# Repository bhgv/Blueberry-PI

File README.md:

to use with spi-nand flash build & flash this Linux tree:

* OpenWRT: https://github.com/bhgv/openwrt

***

main build board now is `Blueberry Pi 7.1.2.esp32.no-lan.gsm-a9g`. because `a9g` gsm module is much better then `sim800c`. because of open source SDK and support of GPS.

but still work-in-progress. not finished.

sources of Linux kernel (4.10.15) for this board(s). preconfigured:
https://github.com/bhgv/linux

precompiled Linux-4.10.15 SD-image with support of fb-graphics an resistive touch:
https://github.com/bhgv/linux/releases/tag/1.0a

exp2_Blueberry Pi 7.1.2.licheepi-zero.esp32.no-lan.gsm-a9g.no-50p
=================================================================
most simplest to assembly choise
* cheap Lichee Pi zero module as CPU and CPU-power module. also used its TFT connector
* ESP32-WROOM as wifi/bluetooth module
* A9/A9G as GSM/GPS module
* connector for cheap popular gt911 capacitive touchscreens (workable driver for gt911 is included to [this Linux](https://github.com/bhgv/linux))
* includes Li-Ion/polimer battery charging/powering circuits

Blueberry Pi 7.1.2.esp32.no-lan
===============================
(not finished yet)
* removed lan port,
* added 50pins fpc RGB connector for popular 7" tfts (AT070TN[90, 91, 92, 93, 94]) in parallel to 40pins one,
* connector for capacitive touchscreens (i2c1),
* power converters for 50pins socket,
* 25% smaller board.
* esp32 now wired as wifi/bluetooth and as io expander-coprocessor.

Blueberry Pi 7.1.1+ESP32-S
==========================
(not finised yet)
* other power controller(s). 3 cheap and easy to solder chips in sot23-6,
* a try to use ESP32-S module as a WiFi/Bluetooth co-processor.

List of compatible (and cheap) LCDs (with touchscreens)
=======================================================
* ? 7" -- MDT7000
* 7" -- TKR7040B
* 7" -- GL070009T0-40

* 6" -- KD060G1-40nc-a5
* 6" -- TM060RDH02

* 5" -- HSD050IDW1-A20
* 5" -- MH0506D
* 5" -- KD50G21-40NT-A1
* 5" -- A26TF9C032169 * A0 -A20
* 5" -- H-H050L-12M
* 5" -- GL050001C0-40
* 5" -- ft050s800480005n-v01
* 5" -- HW800480F-0F-0L-20
* 5" -- hw800480f-0f-0l-10
* 5" -- T050SWV012T
* 5" -- T050SWV015T
* 5" -- FC050S151-01
* 5" -- KD50G23-40NB-A1
* 5" -- HLY050ML115-12A

(
* 6" -- texet tn-811bt

* 5" --
- Window N5 TOP Tablet PC/ N5PRO/ Onda 580
- TeXet T-939HD
- TeXet T-930HD
- TeXet TN-550A
- TeXet TN-511HD
- TeXet TN-521HD
- TeXet TN-610HD
- TeXet TN-611HD
- TeXet TM-650 (100%)
- Explay PN-955
- Explay PN-960
- SHTURMANN Play 500
- IQU Smile
- Lexand Si-515 Pro HD
- Lexand SG-615 PRO HD
- Ritmix
- EasyGo 500Bi (100%)
- lexand str-5350 hd (100%)
- Prestigio Geovision 5500BTFMHD (100%)
- Prestigio GeoVision 5600GPRSHD
- Explay SLK5
- JXD S5300
- TurboGames New
- EXEQ SET
)

Blueberry Pi 7.1+axp203
=======================
is the Blueberry Pi 7.1 board but with AXP203 power controller, not EA3036. and has DC-DC step down (5-12v) on power input.

Blueberry PI 7.1
================

Added:
------
* LVDS interface with cheap SN65LVDS84 serialiser,
* resistive touchscreen controller TSC2003 + pinheader for resistive touch,
* flash w25q128,
* more popular MicroSD card slot,
* datasheets for them

Removed:
--------
* pinheader for OV7670

Blueberry PI
============
Another fruit single board computer (SBC), based on the Allwinner V3s system on a chip (SOC).
The Allwinner V3s comes in an easy to solder 128pin TQFP package.

The Blueberry PI features:

- 100 mbps Ethernet
- 1 USB Host Port / 1 mini USB port
- MIPI CSI interface (unfortunately no support in the linux kernel yet)
- Pinheader for an OV2640 and an OV7670
- Wifi and bluetooth
- RGB interface for connecting displays
- Audio jack
- an onboard microphone
- four buttons for play, pause, next and previous
- a Raspberry PI compatible header
- SPI Flash
- SD card slot

The Blueberry PI can boot from an SD card or SPI Flash.
Since the V3s doesn't have a standard video output, I'm planning on creating a video addon board which provides VGA or HDMI. In combination with the ADV7611 it is possible to capture HDMI.

If you have any questions email me at marcel[dot]thuermer(at)smail[dot]emt[dot]h[minus]brs[dot]de

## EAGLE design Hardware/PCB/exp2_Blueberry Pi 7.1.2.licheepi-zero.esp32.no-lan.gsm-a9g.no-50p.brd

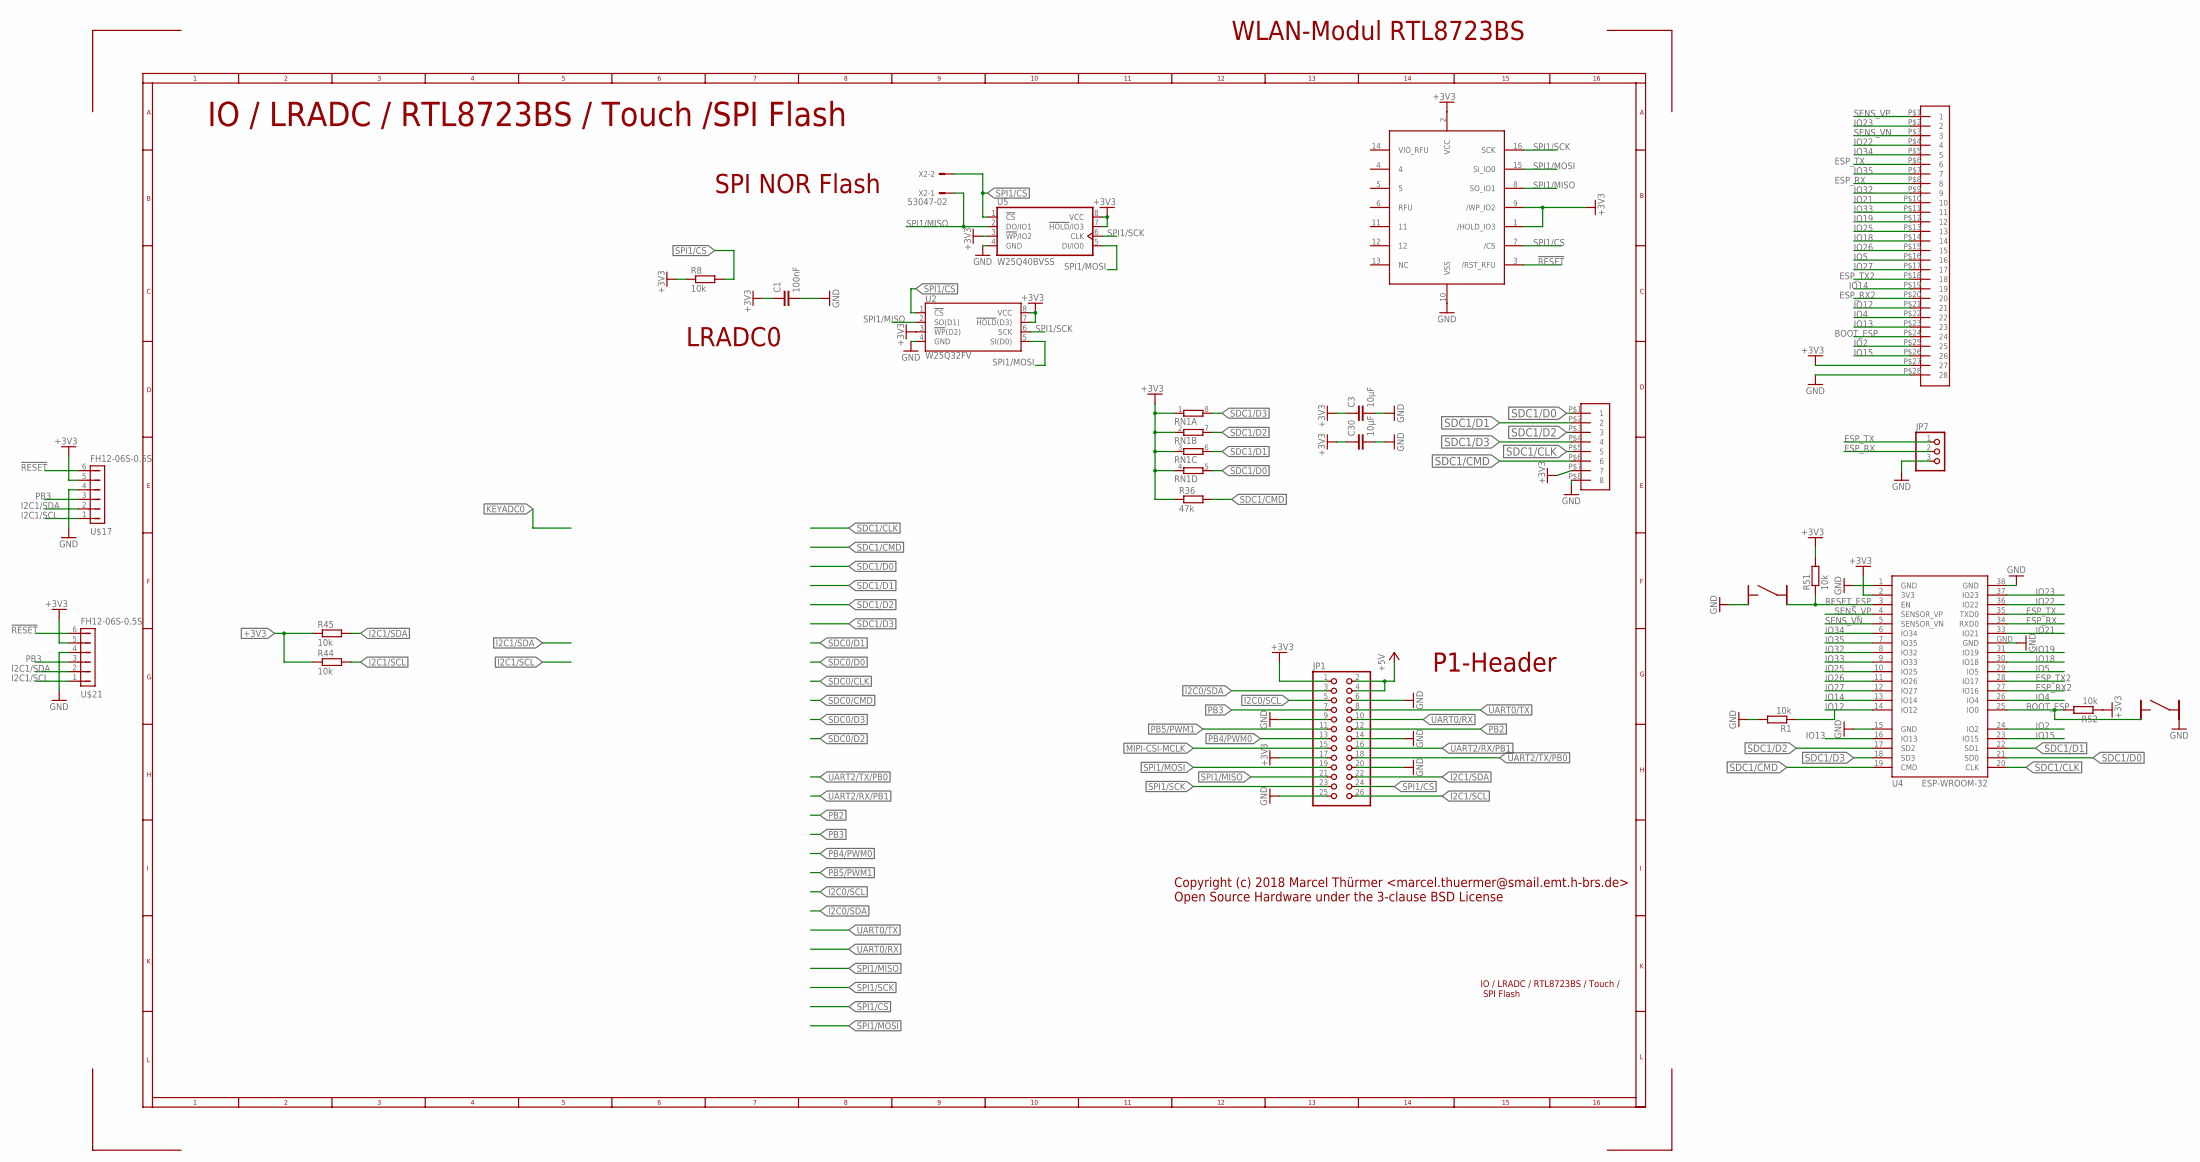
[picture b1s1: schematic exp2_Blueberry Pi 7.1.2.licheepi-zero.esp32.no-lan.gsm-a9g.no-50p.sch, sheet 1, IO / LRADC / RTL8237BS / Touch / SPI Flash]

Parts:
C1: 100nF; C0603
C3, C30: 10µF; C0805
JP1: PINHD-2X13; 2X13
JP7: PINHD-1X3M; 1X03M
R1, R8, R44, R45, R51, R52: 10k; R0603
R36: 47k; R0603
RN1: 4R-NEXB38V; EXB38V
S-BOOT-ESP: BUTTON_3X3MM_4PINS; BUT_3X3_4PINS
S-RST-ESP: BUTTON_3X3MM_4PINS; BUT_3X3_4PINS
U2: W25Q32FV; WSON8-6X5MM
U4: ESP-WROOM-32
U5: W25Q40BVSS; SO08-SS
U$3: HDR-1.27MM-142; HDR-1.27MM-19*2
U$4: HDR-1.27MM-42; HDR-1.27MM-4*2
U$16: S25FL256S; WSOIC-16
U$17, U$21: FH12-06S-0.5S; FH12-6S-0.5SH
X2: 53047-02

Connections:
!RESET: U$16.3 (/RST_RFU), U$17.6, U$21.6; also elsewhere on the board
+3V3: C1.1, C3.1, C30.1, JP1.1, JP1.17, R8.1, R36.1, R44.1, R45.1, R51.2, R52.1, RN1.1, RN1.2 (1), RN1.3 (1), RN1.4 (1), U2.3 (!WP!(D2)), U2.7 (!HOLD!(D3)), U2.8 (VCC), U4.2 (3V3), U5.3 (!WP!/IO2), U5.7 (!HOLD!/IO3), U5.8 (VCC), U$3.P$27 (27), U$4.P$7 (7), U$16.1 (/HOLD_IO3), U$16.2 (VCC), U$16.9 (/WP_IO2), U$17.5, U$21.5; also elsewhere on the board
+5V: JP1.2, JP1.4; also elsewhere on the board
BOOT_ESP: R52.2, S-BOOT-ESP.P$1, U4.25 (IO0), U$3.P$24 (24)
ESP_RX: JP7.2, U4.34 (RXD0), U$3.P$8 (8)
ESP_RX2: U4.27 (IO16), U$3.P$20 (20); also elsewhere on the board
ESP_TX: JP7.1, U4.35 (TXD0), U$3.P$6 (6)
ESP_TX2: U4.28 (IO17), U$3.P$18 (18); also elsewhere on the board
GND: C1.2, C3.2, C30.2, JP1.6, JP1.9, JP1.14, JP1.20, JP1.25, JP7.3, R1.2, S-BOOT-ESP.P$2, S-RST-ESP.P$1, U2.4 (GND), U4.1 (GND), U4.15 (GND), U4.38 (GND), U4.GND, U5.4 (GND), U$3.P$28 (28), U$4.P$8 (8), U$16.10 (VSS), U$17.4, U$21.4; also elsewhere on the board
I2C0/SCL: JP1.5; also elsewhere on the board
I2C0/SDA: JP1.3; also elsewhere on the board
I2C1/SCL: JP1.26, R44.2, U$17.1, U$21.1; also elsewhere on the board
I2C1/SDA: JP1.22, R45.2, U$17.2, U$21.2; also elsewhere on the board
IO2: U4.24 (IO2), U$3.P$25 (25)
IO4: U4.26 (IO4), U$3.P$22 (22)
IO5: U4.29 (IO5), U$3.P$16 (16)
IO12: R1.1, U4.14 (IO12), U$3.P$21 (21)
IO13: U4.16 (IO13), U$3.P$23 (23)
IO14: U4.13 (IO14), U$3.P$19 (19); also elsewhere on the board
IO15: U4.23 (IO15), U$3.P$26 (26)
IO18: U4.30 (IO18), U$3.P$14 (14)
IO19: U4.31 (IO19), U$3.P$12 (12)
IO21: U4.33 (IO21), U$3.P$10 (10)
IO22: U4.36 (IO22), U$3.P$4 (4)
IO23: U4.37 (IO23), U$3.P$2 (2)
IO25: U4.10 (IO25), U$3.P$13 (13)
IO26: U4.11 (IO26), U$3.P$15 (15)
IO27: U4.12 (IO27), U$3.P$17 (17); also elsewhere on the board
IO32: U4.8 (IO32), U$3.P$9 (9)
IO33: U4.9 (IO33), U$3.P$11 (11)
IO34: U4.6 (IO34), U$3.P$5 (5)
IO35: U4.7 (IO35), U$3.P$7 (7)
MIPI-CSI-MCLK: JP1.15
PB2: JP1.12; also elsewhere on the board
PB3: JP1.7, U$17.3, U$21.3; also elsewhere on the board
PB4/PWM0: JP1.13; also elsewhere on the board
PB5/PWM1: JP1.11; also elsewhere on the board
RESET_ESP: R51.1, S-RST-ESP.P$2, U4.3 (EN)
SDC1/CLK: U4.20 (CLK), U$4.P$5 (5); also elsewhere on the board
SDC1/CMD: R36.2, U4.19 (CMD), U$4.P$6 (6); also elsewhere on the board
SDC1/D0: RN1.5 (2), U4.21 (SD0), U$4.P$1 (1); also elsewhere on the board
SDC1/D1: RN1.6 (2), U4.22 (SD1), U$4.P$2 (2); also elsewhere on the board
SDC1/D2: RN1.7 (2), U4.17 (SD2), U$4.P$3 (3); also elsewhere on the board
SDC1/D3: RN1.8 (2), U4.18 (SD3), U$4.P$4 (4); also elsewhere on the board
SENS_VN: U4.5 (SENSOR_VN), U$3.P$3 (3)
SENS_VP: U4.4 (SENSOR_VP), U$3.P$1 (1)
SPI1/CS: JP1.24, R8.2, U2.1 (!CS!), U5.1 (!CS!), U$16.7 (/CS), X2.2; also elsewhere on the board
SPI1/MISO: JP1.21, U2.2 (SO(D1)), U5.2 (DO/IO1), U$16.8 (SO_IO1), X2.1; also elsewhere on the board
SPI1/MOSI: JP1.19, U2.5 (SI(D0)), U5.5 (DI/IO0), U$16.15 (SI_IO0); also elsewhere on the board
SPI1/SCK: JP1.23, U2.6 (SCK), U5.6 (CLK), U$16.16 (SCK); also elsewhere on the board
UART0/RX: JP1.10; also elsewhere on the board
UART0/TX: JP1.8; also elsewhere on the board
UART2/RX/PB1: JP1.16; also elsewhere on the board
UART2/TX/PB0: JP1.18; also elsewhere on the board

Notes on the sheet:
IO / LRADC / RTL8723BS / Touch / SPI Flash
Copyright (c) 2018 Marcel Thürmer <marcel.thuermer@smail.emt.h-brs.de> Open Source Hardware under the 3-clause BSD License
SPI NOR Flash
WLAN-Modul RTL8723BS
P1-Header
LRADC0
IO / LRADC / RTL8723BS / Touch /SPI Flash

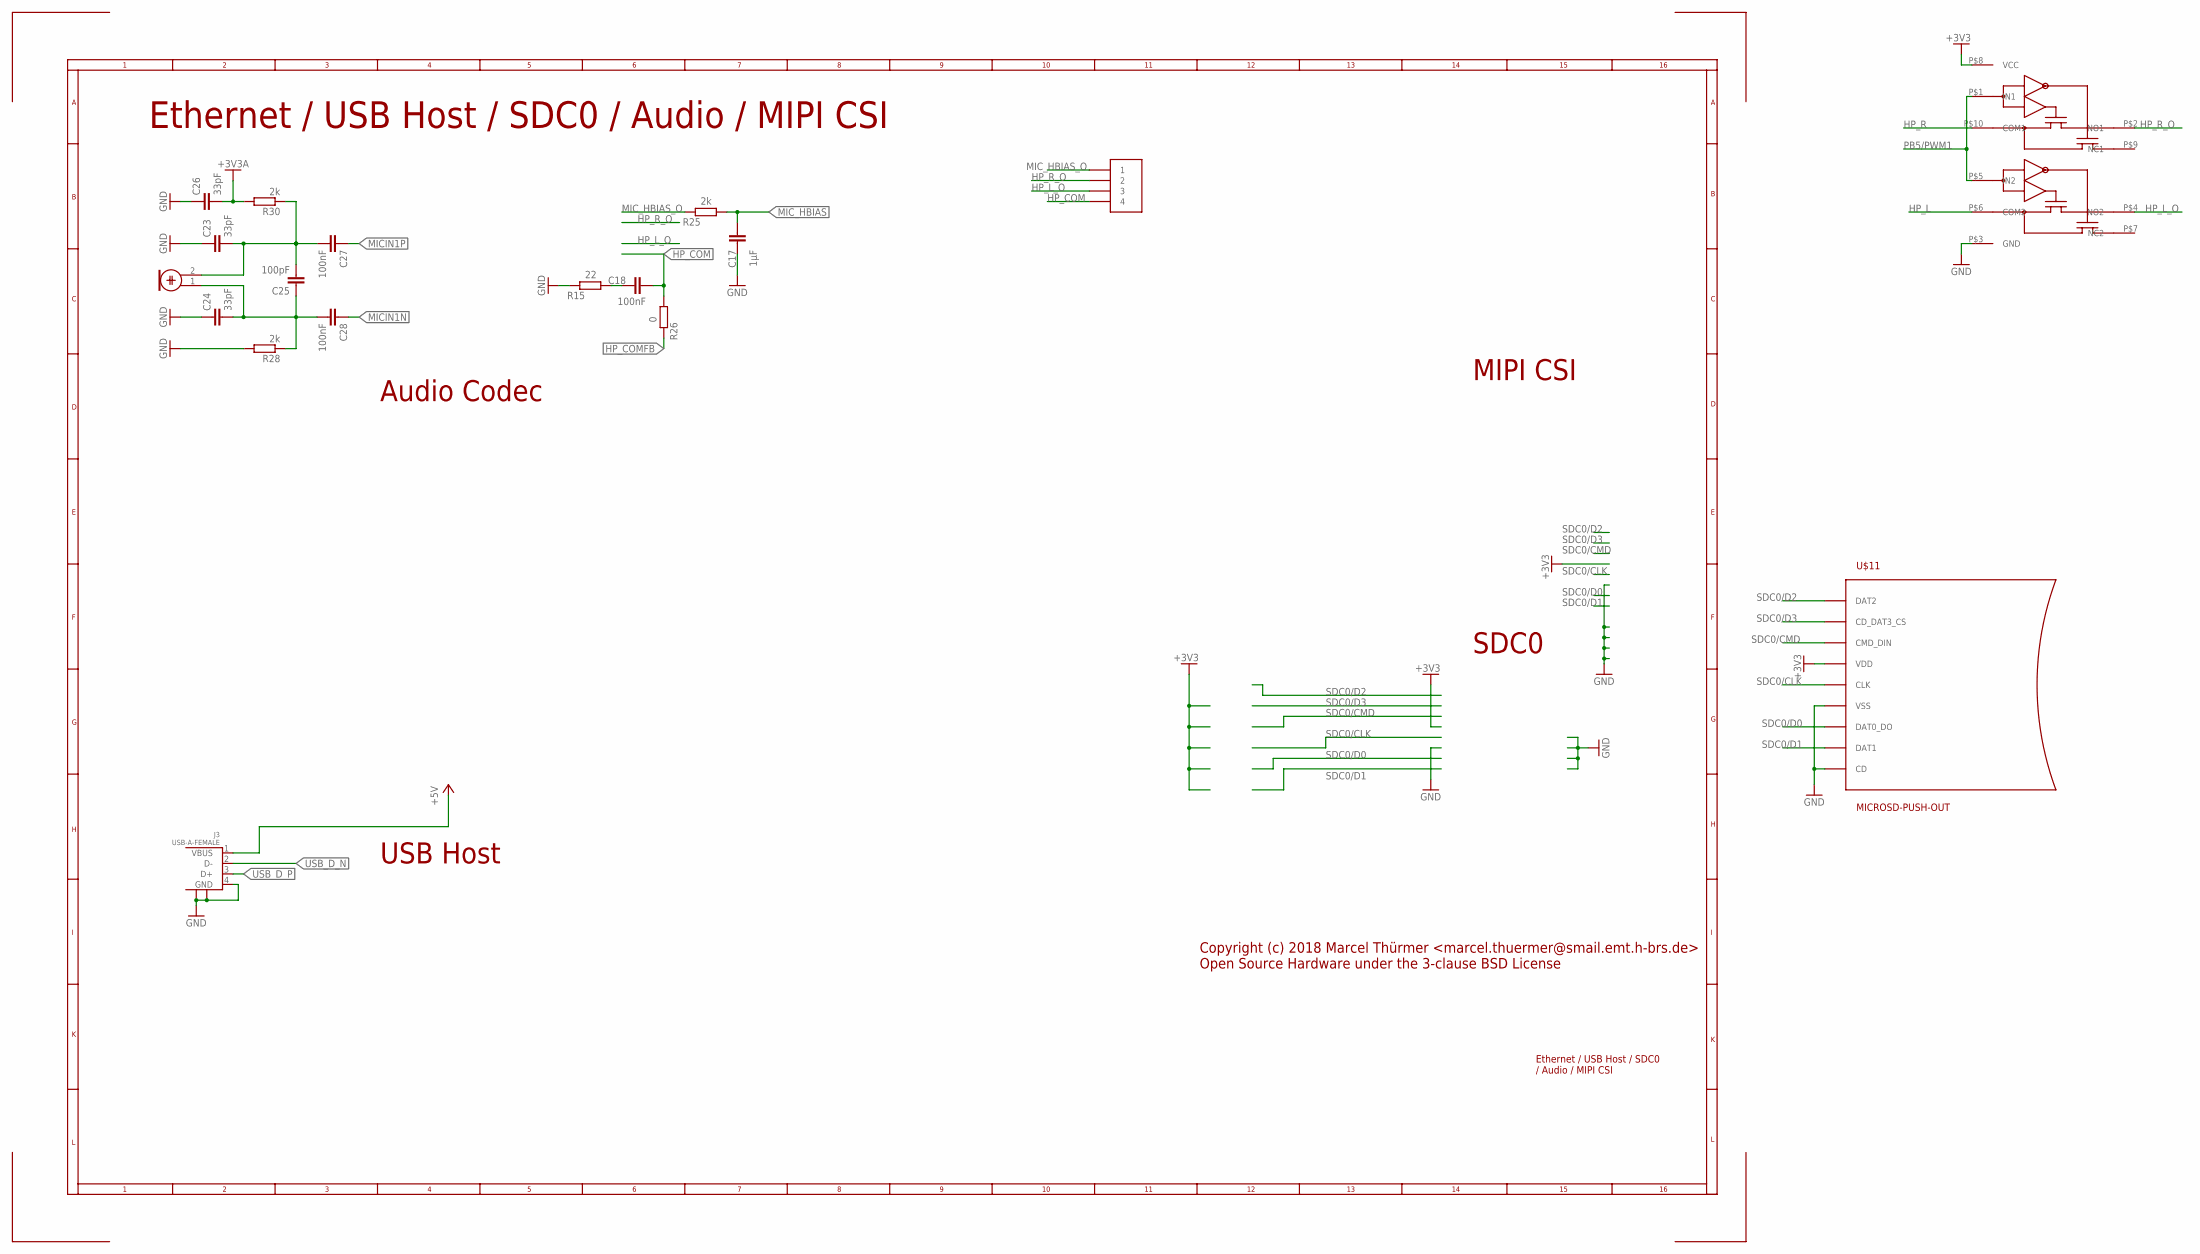
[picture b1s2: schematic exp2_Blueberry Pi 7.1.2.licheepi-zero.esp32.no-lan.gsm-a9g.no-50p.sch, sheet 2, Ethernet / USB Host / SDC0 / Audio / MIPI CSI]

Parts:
C17: 1µF; C0603
C18, C27, C28: 100nF; C0603
C23, C24, C26: 33pF; C0603
C25: 100pF; C0603
J3: USB-A-FEMALE
J-AUDIO: HDR-1.27MM-14; HDR-1.27MM-1*4
MIC: ELECTRET_MICROPHON-F6035AP; F6035AP
R15: 22; R0603
R25, R28, R30: 2k; R0603
R26: 0; R0603
U$11: MICROSD-PUSH-OUT
U$24: TS5A23157

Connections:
+3V3: U$11.4 (VDD), U$24.P$8 (VCC); also elsewhere on the board
+3V3A: C26.2, R30.2
+5V: J3.1 (VBUS); also elsewhere on the board
GND: C17.2, C23.1, C24.1, C26.1, J3.4 (GND), J3.P$1, J3.P$2, R15.1, R28.2, U$11.6 (VSS), U$11.CD, U$11.G1 (VSS), U$11.G2 (VSS), U$11.G3 (VSS), U$11.G4 (VSS), U$24.P$3 (GND); also elsewhere on the board
HP_COM: C18.2, J-AUDIO.P$4 (4), R26.2; also elsewhere on the board
HP_COMFB: R26.1; also elsewhere on the board
HP_L: U$24.P$6 (COM2); also elsewhere on the board
HP_L_O: J-AUDIO.P$3 (3), U$24.P$4 (NO2)
HP_R: U$24.P$10 (COM1); also elsewhere on the board
HP_R_O: J-AUDIO.P$2 (2), U$24.P$2 (NO1)
MICIN1N: C28.1; also elsewhere on the board
MICIN1P: C27.1; also elsewhere on the board
MIC_HBIAS: C17.1, R25.2; also elsewhere on the board
MIC_HBIAS_O: J-AUDIO.P$1 (1), R25.1
unnamed: C18.1, R15.2
unnamed: C23.2, C25.2, C27.2, MIC.2, R30.1
unnamed: C24.2, C25.1, C28.2, MIC.1, R28.1
PB5/PWM1: U$24.P$1 (IN1), U$24.P$5 (IN2); also elsewhere on the board
SDC0/CLK: U$11.5 (CLK); also elsewhere on the board
SDC0/CMD: U$11.3 (CMD_DIN); also elsewhere on the board
SDC0/D0: U$11.7 (DAT0_DO); also elsewhere on the board
SDC0/D1: U$11.8 (DAT1); also elsewhere on the board
SDC0/D2: U$11.1 (DAT2); also elsewhere on the board
SDC0/D3: U$11.2 (CD_DAT3_CS); also elsewhere on the board
USB_D_N: J3.2 (D-); also elsewhere on the board
USB_D_P: J3.3 (D+); also elsewhere on the board

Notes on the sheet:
Ethernet / USB Host / SDC0 / Audio / MIPI CSI
USB Host
Audio Codec
MIPI CSI
SDC0
Copyright (c) 2018 Marcel Thürmer <marcel.thuermer@smail.emt.h-brs.de> Open Source Hardware under the 3-clause BSD License
Ethernet / USB Host / SDC0 / Audio / MIPI CSI

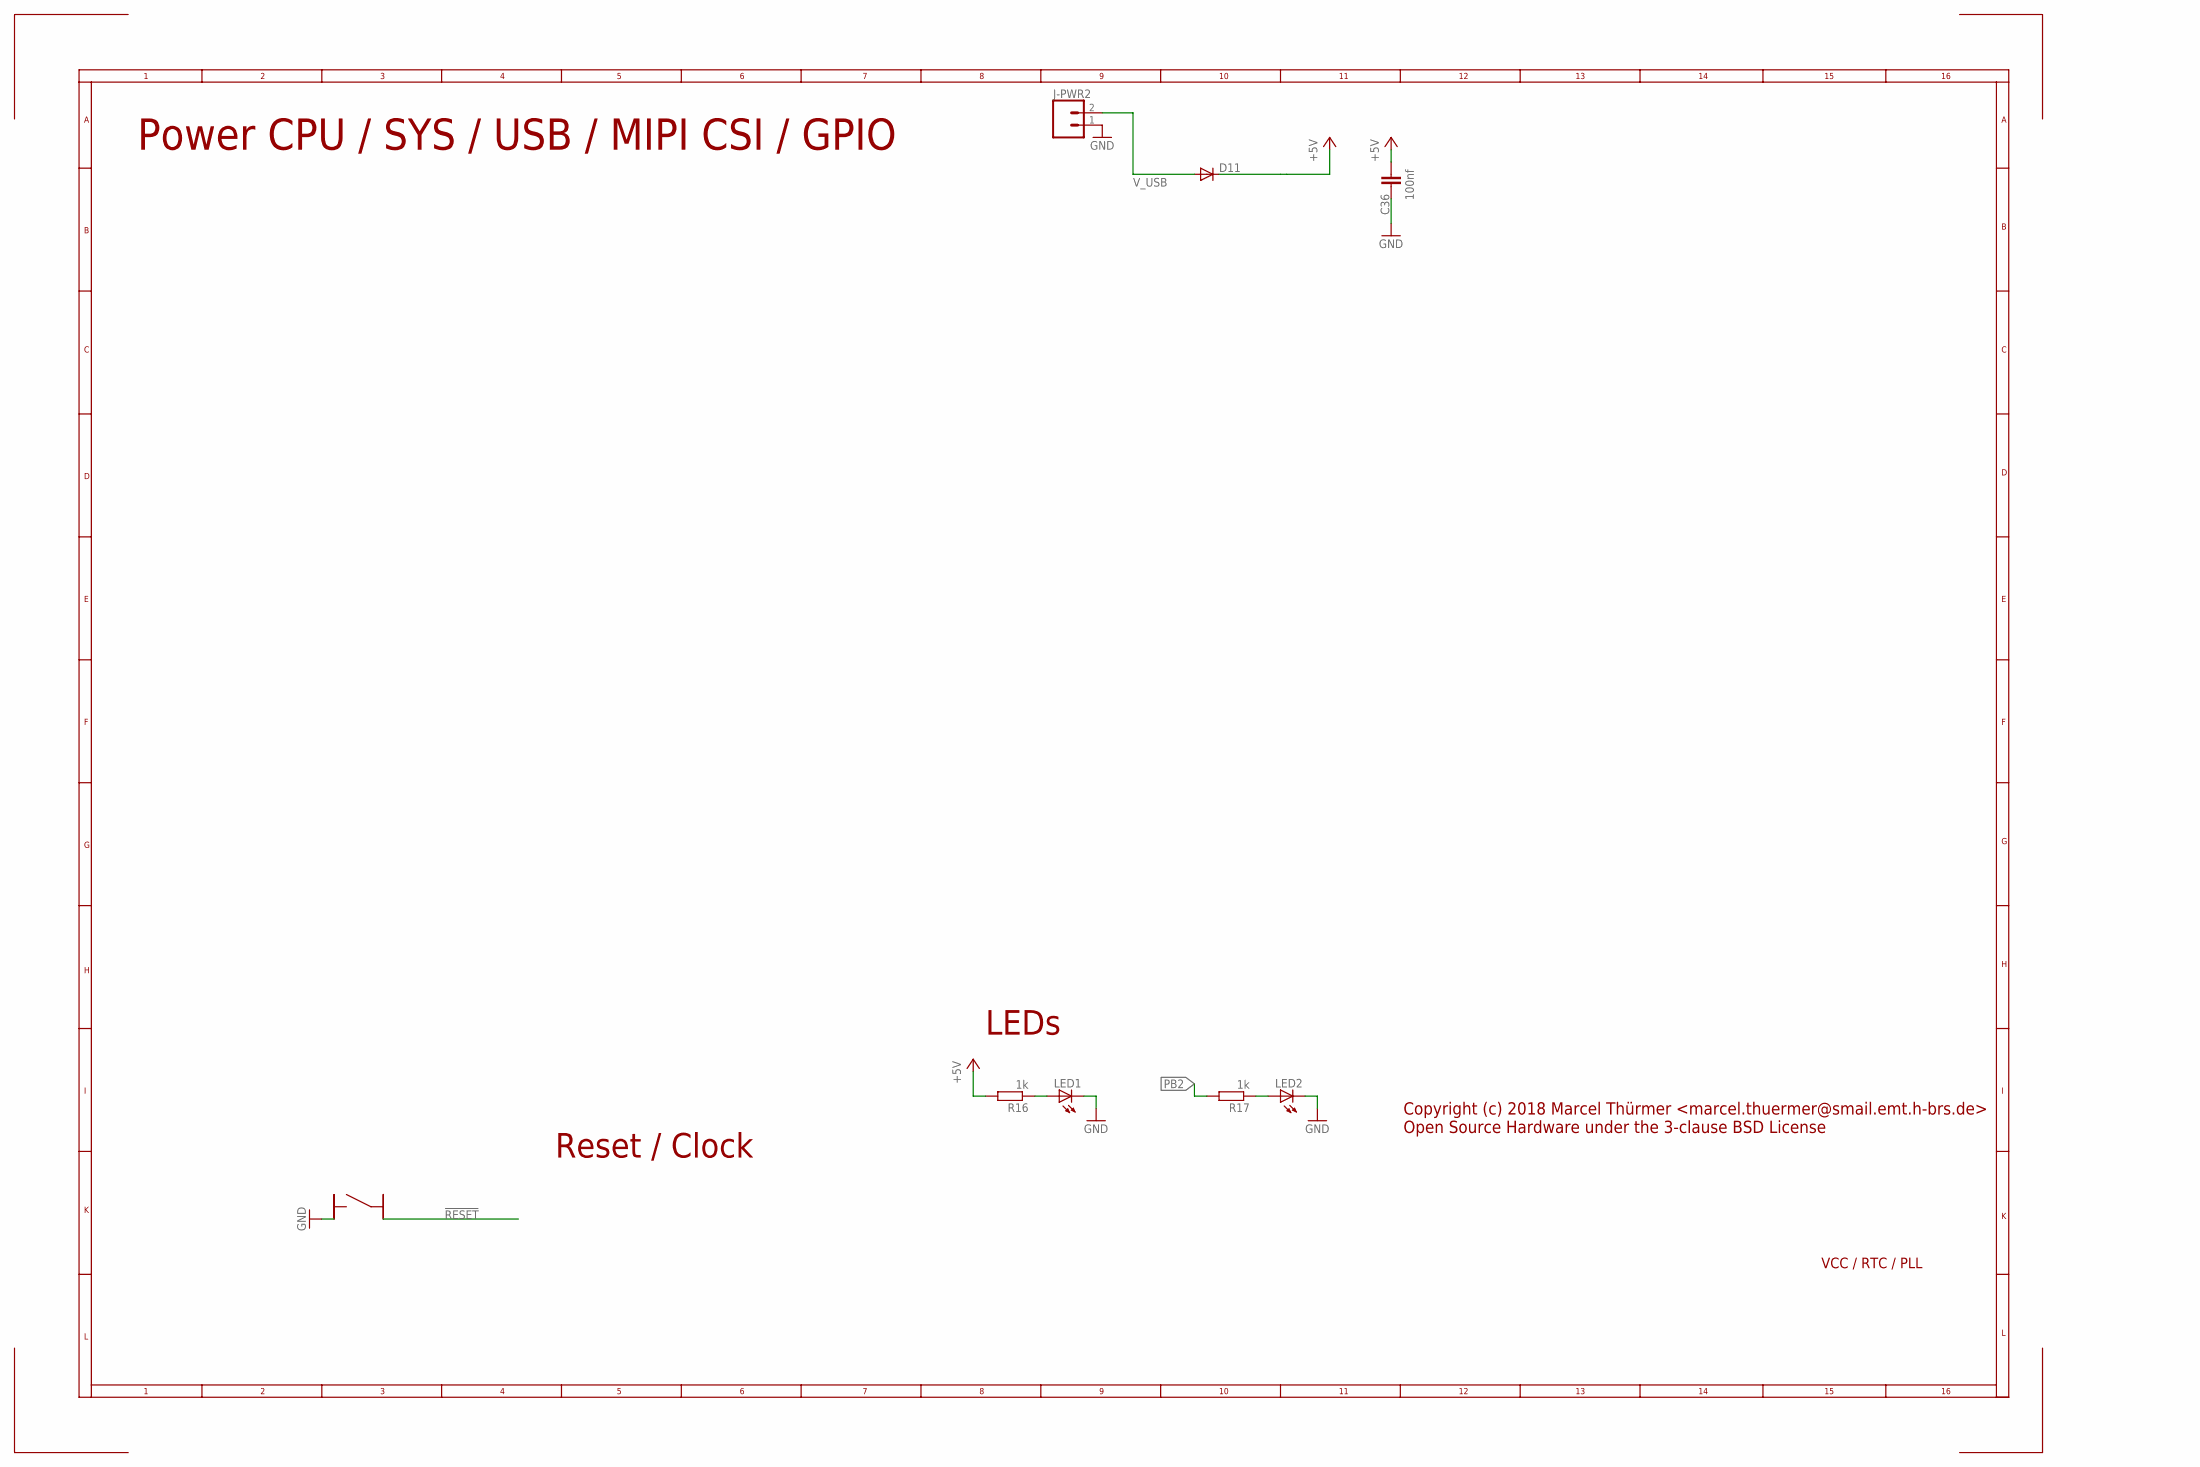
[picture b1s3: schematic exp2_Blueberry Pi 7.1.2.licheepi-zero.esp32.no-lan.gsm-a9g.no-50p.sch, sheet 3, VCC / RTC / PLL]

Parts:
C36: 100nf; C0603
D11: DIODE-SOD323-W; SOD323-W
J-PWR2: CONN_02; 1X02
LED1, LED2: LEDCHIPLED_0805; CHIPLED_0805
R16, R17: 1k; R0603
S-RST: BUTTON_3X3MM_4PINS; BUT_3X3_4PINS

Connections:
!RESET: S-RST.P$2; also elsewhere on the board
+5V: C36.1, D11.C, R16.2; also elsewhere on the board
GND: C36.2, J-PWR2.1, LED1.C, LED2.C, S-RST.P$1; also elsewhere on the board
unnamed: LED1.A, R16.1
unnamed: LED2.A, R17.1
PB2: R17.2; also elsewhere on the board
V_USB: D11.A, J-PWR2.2; also elsewhere on the board

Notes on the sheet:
VCC / RTC / PLL
Power CPU / SYS / USB / MIPI CSI / GPIO
Copyright (c) 2018 Marcel Thürmer <marcel.thuermer@smail.emt.h-brs.de> Open Source Hardware under the 3-clause BSD License
Reset / Clock
LEDs

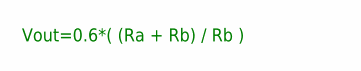
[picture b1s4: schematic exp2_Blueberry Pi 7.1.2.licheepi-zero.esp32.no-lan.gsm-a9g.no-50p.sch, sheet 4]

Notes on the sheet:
Vout=0.6*( (Ra + Rb) / Rb )

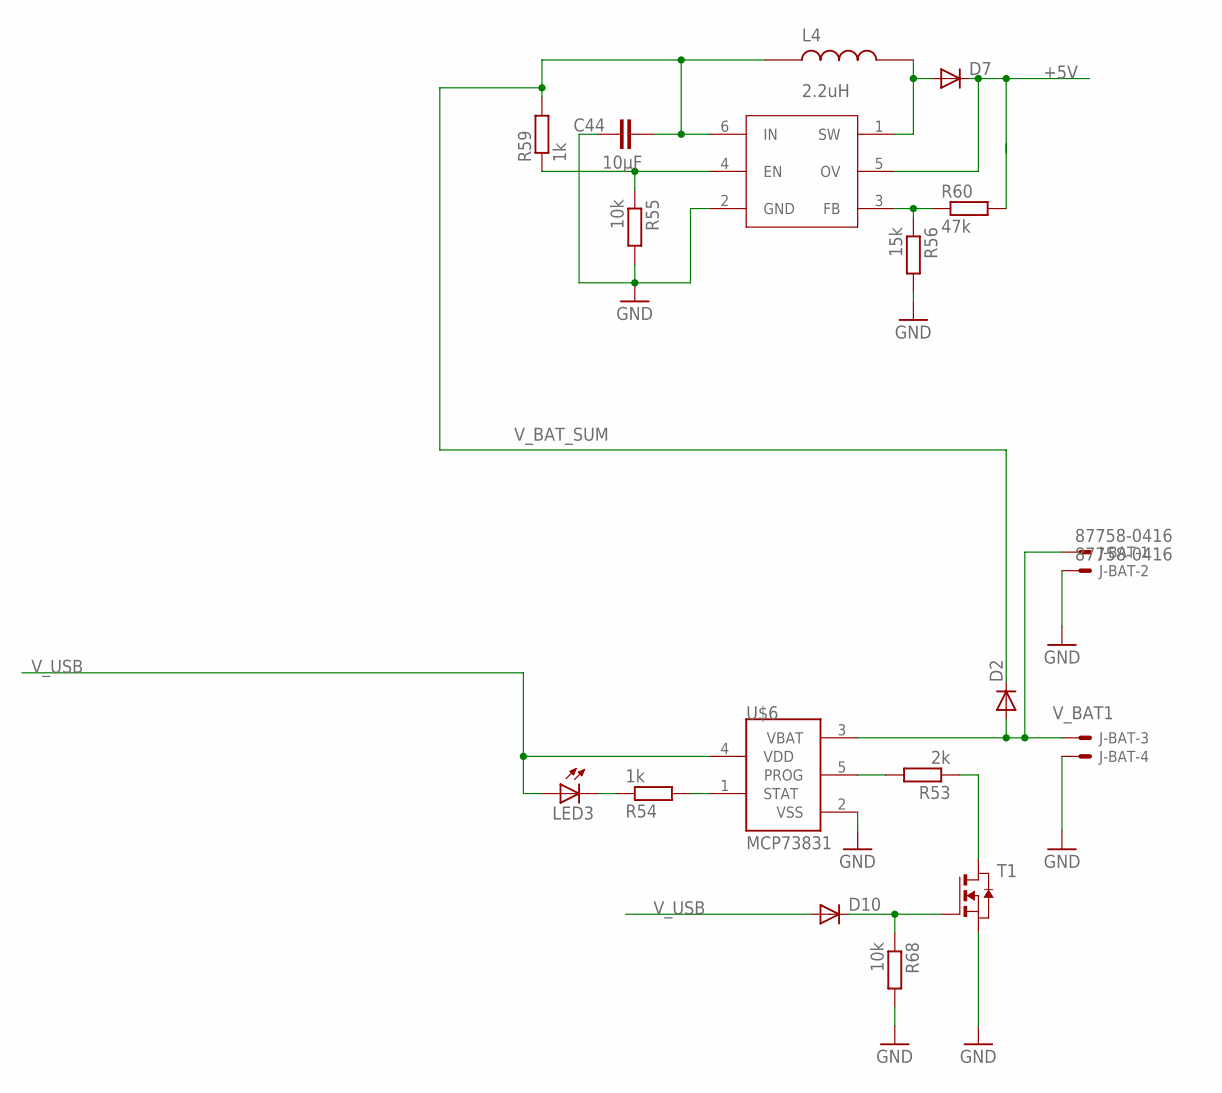
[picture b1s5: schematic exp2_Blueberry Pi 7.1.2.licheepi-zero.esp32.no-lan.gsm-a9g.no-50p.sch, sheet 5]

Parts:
C44: 10µF; C0805
D2: DIODE-DO214AC; DO214AC
D7, D10: DIODE-SOD323-W; SOD323-W
J-BAT: 87758-0416
L4: 2.2uH; CD32
LED3: LEDCHIPLED_0805; CHIPLED_0805
R53: 2k; R0603
R54, R59: 1k; R0603
R55, R68: 10k; R0603
R56: 15k; R0603
R60: 47k; R0603
T1: NMOSSOT23; SOT-23
U$6: MCP73831; SOT23-5L
U$10: PT4101; SOT23-6

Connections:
+5V: D7.C, R60.2, U$10.5 (OV); also elsewhere on the board
GND: C44.2, J-BAT.2, J-BAT.4, R55.2, R56.2, R68.2, T1.2 (S), U$6.2 (VSS), U$10.2 (GND); also elsewhere on the board
unnamed: R53.1, T1.1 (D)
unnamed: R56.1, R60.1, U$10.3 (FB)
unnamed: R55.1, R59.1, U$10.4 (EN)
unnamed: D7.A, L4.P$2, U$10.1 (SW)
unnamed: D10.C, R68.1, T1.3 (G)
unnamed: R53.2, U$6.5 (PROG)
unnamed: LED3.C, R54.1
unnamed: R54.2, U$6.1 (STAT)
V_BAT1: D2.A, J-BAT.1, J-BAT.3, U$6.3 (VBAT)
V_BAT_SUM: C44.1, D2.C, L4.P$1, R59.2, U$10.6 (IN); also elsewhere on the board
V_USB: D10.A, LED3.A, U$6.4 (VDD); also elsewhere on the board

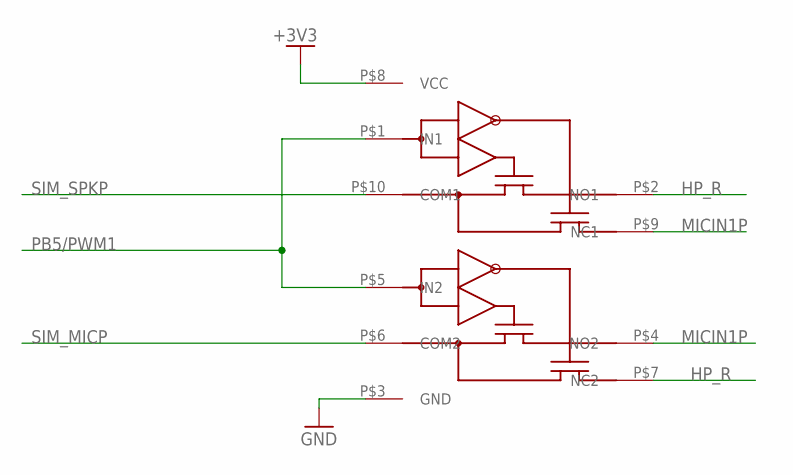
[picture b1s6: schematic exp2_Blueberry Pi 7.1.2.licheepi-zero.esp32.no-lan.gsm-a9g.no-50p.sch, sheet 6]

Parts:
U$19: TS5A23157

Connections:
+3V3: U$19.P$8 (VCC); also elsewhere on the board
GND: U$19.P$3 (GND); also elsewhere on the board
HP_R: U$19.P$2 (NO1), U$19.P$7 (NC2); also elsewhere on the board
MICIN1P: U$19.P$4 (NO2), U$19.P$9 (NC1); also elsewhere on the board
PB5/PWM1: U$19.P$1 (IN1), U$19.P$5 (IN2); also elsewhere on the board
SIM_MICP: U$19.P$6 (COM2); also elsewhere on the board
SIM_SPKP: U$19.P$10 (COM1); also elsewhere on the board

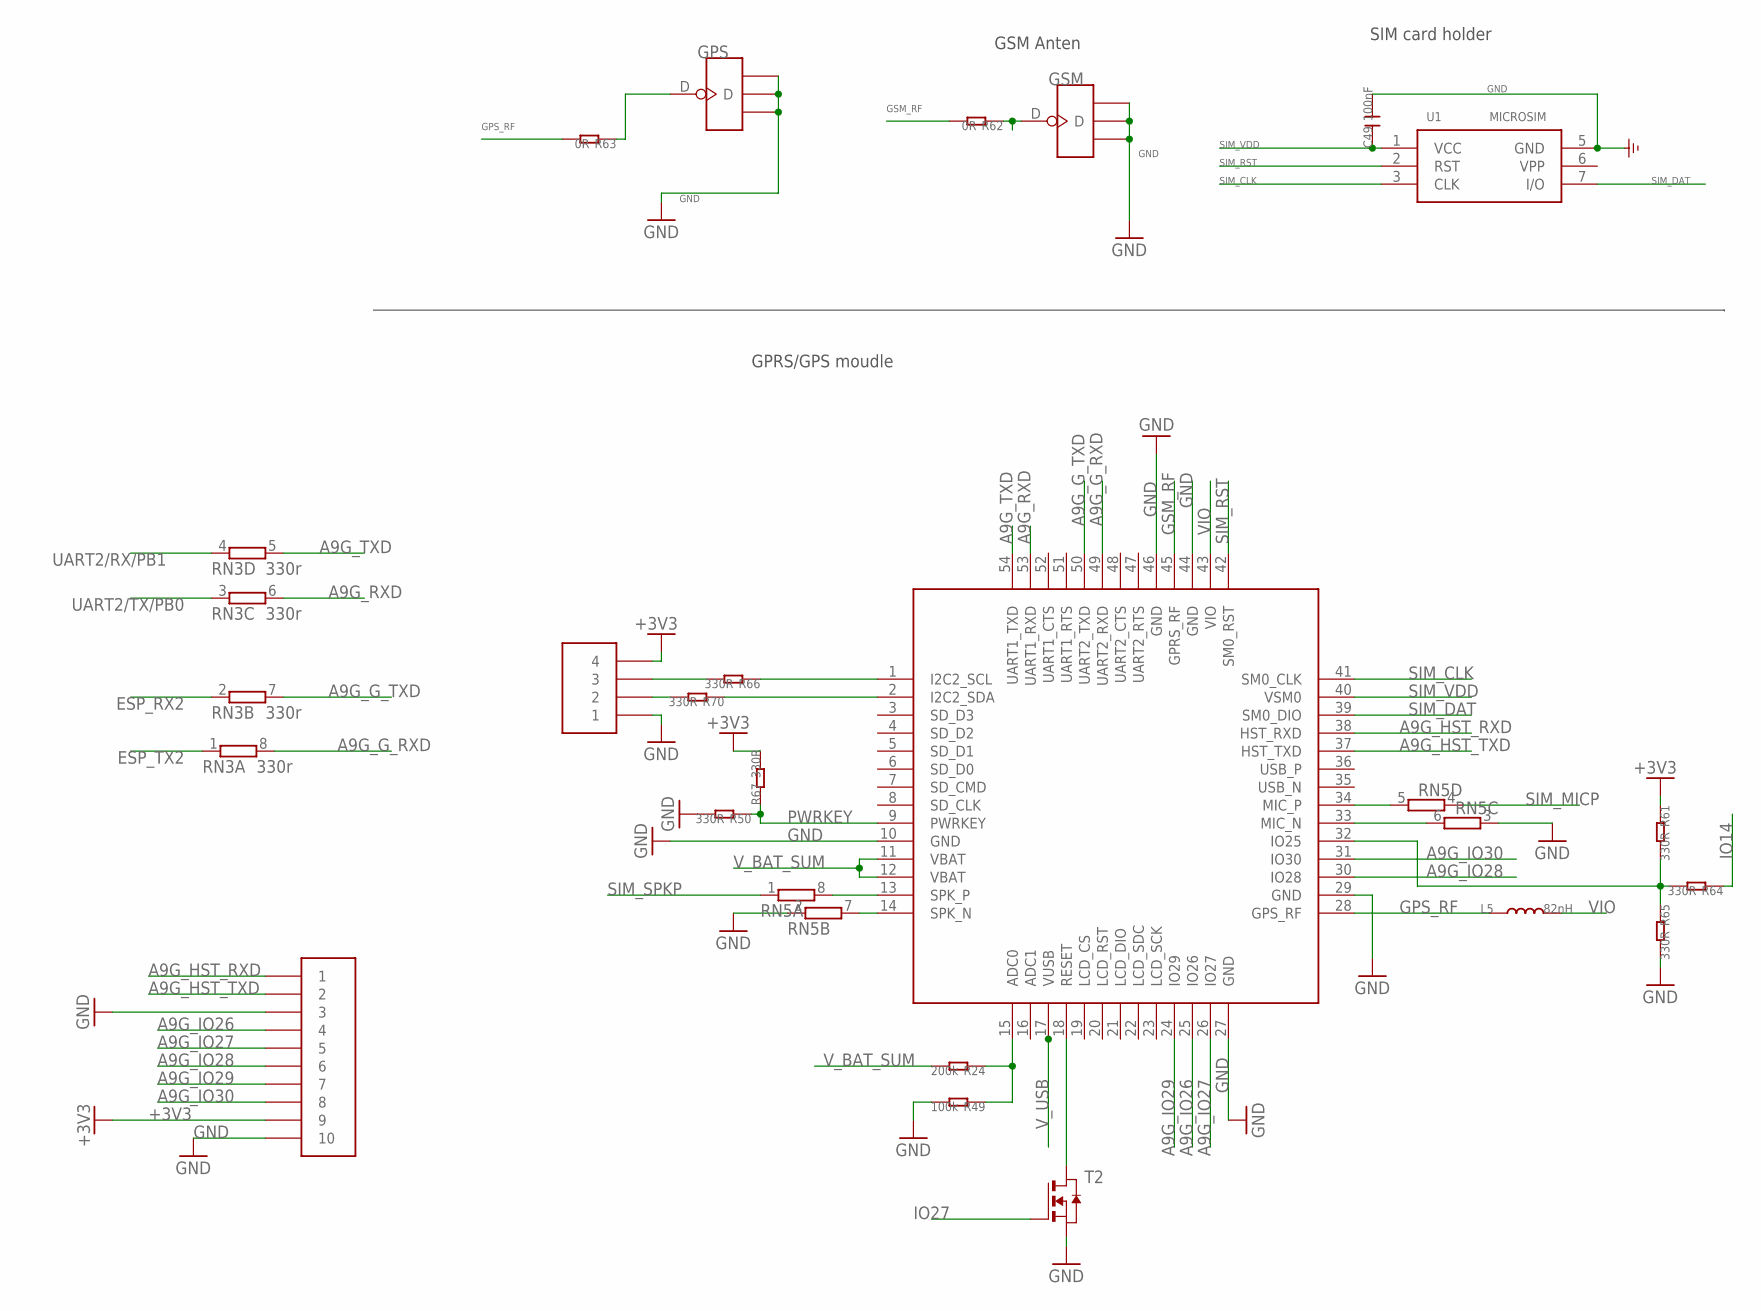
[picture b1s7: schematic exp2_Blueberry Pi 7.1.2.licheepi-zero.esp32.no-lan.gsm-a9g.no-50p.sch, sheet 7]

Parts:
C49: 100nF; C0603
DBG-COM1: HDR-1.27MM-110; HDR-1.27MM-1*10
GPS: ANTENNA-U-FL; 4P-U-FL
GSM: ANTENNA-U-FL; 4P-U-FL
L5: 82nH; L0603
R24: 200k; R0603
R49: 100k; R0603
R50, R61, R64, R65, R66, R67, R70: 330R; R0603
R62, R63: 0R; R0603
RN3: 330r; EXB38V
RN5: 4R-NEXB38V; EXB38V
T2: NMOSSOT23; SOT-23
U1: MICROSIM
U6: A9G
U$20: HDR-1.27MM-14; HDR-1.27MM-1*4

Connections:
+3V3: DBG-COM1.P$9 (9), R61.1, R67.2, U$20.P$4 (4); also elsewhere on the board
A9G_G_RXD: RN3.8 (2), U6.49 (UART2_RXD)
A9G_G_TXD: RN3.7 (2), U6.50 (UART2_TXD)
A9G_HST_RXD: DBG-COM1.P$1 (1), U6.38 (HST_RXD)
A9G_HST_TXD: DBG-COM1.P$2 (2), U6.37 (HST_TXD)
A9G_IO26: DBG-COM1.P$4 (4), U6.25 (IO26)
A9G_IO27: DBG-COM1.P$5 (5), U6.26 (IO27)
A9G_IO28: DBG-COM1.P$6 (6), U6.30 (IO28)
A9G_IO29: DBG-COM1.P$7 (7), U6.24 (IO29)
A9G_IO30: DBG-COM1.P$8 (8), U6.31 (IO30)
A9G_RXD: RN3.6 (2), U6.53 (UART1_RXD)
A9G_TXD: RN3.5 (2), U6.54 (UART1_TXD)
ESP_RX2: RN3.2 (1); also elsewhere on the board
ESP_TX2: RN3.1; also elsewhere on the board
GND: C49.2, DBG-COM1.P$3 (3), DBG-COM1.P$10 (10), GPS.GND1, GPS.GND2, GPS.GND3, GSM.GND1, GSM.GND2, GSM.GND3, R49.2, R50.2, R65.2, RN5.2 (1), RN5.3 (1), T2.2 (S), U1.5 (GND), U6.10 (GND), U6.27 (GND), U6.29 (GND), U6.44 (GND), U6.46 (GND), U$20.P$1 (1); also elsewhere on the board
GPS_RF: L5.1, R63.2, U6.28 (GPS_RF)
GSM_RF: R62.2, U6.45 (GPRS_RF)
IO14: R64.1; also elsewhere on the board
IO27: T2.3 (G); also elsewhere on the board
unnamed: R24.1, R49.1, U6.15 (ADC0)
unnamed: RN5.6 (2), U6.33 (MIC_N)
unnamed: RN5.7 (2), U6.14 (SPK_N)
unnamed: R61.2, R64.2, R65.1, U6.32 (IO25)
unnamed: T2.1 (D), U6.18 (RESET)
unnamed: RN5.8 (2), U6.13 (SPK_P)
unnamed: R66.1, U6.1 (I2C2_SCL)
unnamed: GSM.D, R62.1
unnamed: GPS.D, R63.1
unnamed: R70.2, U$20.P$2 (2)
unnamed: R70.1, U6.2 (I2C2_SDA)
unnamed: RN5.5 (2), U6.34 (MIC_P)
unnamed: R66.2, U$20.P$3 (3)
PWRKEY: R50.1, R67.1, U6.9 (PWRKEY)
SIM_CLK: U1.3 (CLK), U6.41 (SM0_CLK)
SIM_DAT: U1.7 (I/O), U6.39 (SM0_DIO)
SIM_MICP: RN5.4 (1); also elsewhere on the board
SIM_RST: U1.2 (RST), U6.42 (SM0_RST)
SIM_SPKP: RN5.1; also elsewhere on the board
SIM_VDD: C49.1, U1.1 (VCC), U6.40 (VSM0)
UART2/RX/PB1: RN3.4 (1); also elsewhere on the board
UART2/TX/PB0: RN3.3 (1); also elsewhere on the board
VIO: L5.2, U6.43 (VIO)
V_BAT_SUM: R24.2, U6.11 (VBAT), U6.12 (VBAT); also elsewhere on the board
V_USB: U6.17 (VUSB); also elsewhere on the board

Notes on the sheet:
SIM card holder
GSM Anten
GPRS/GPS moudle

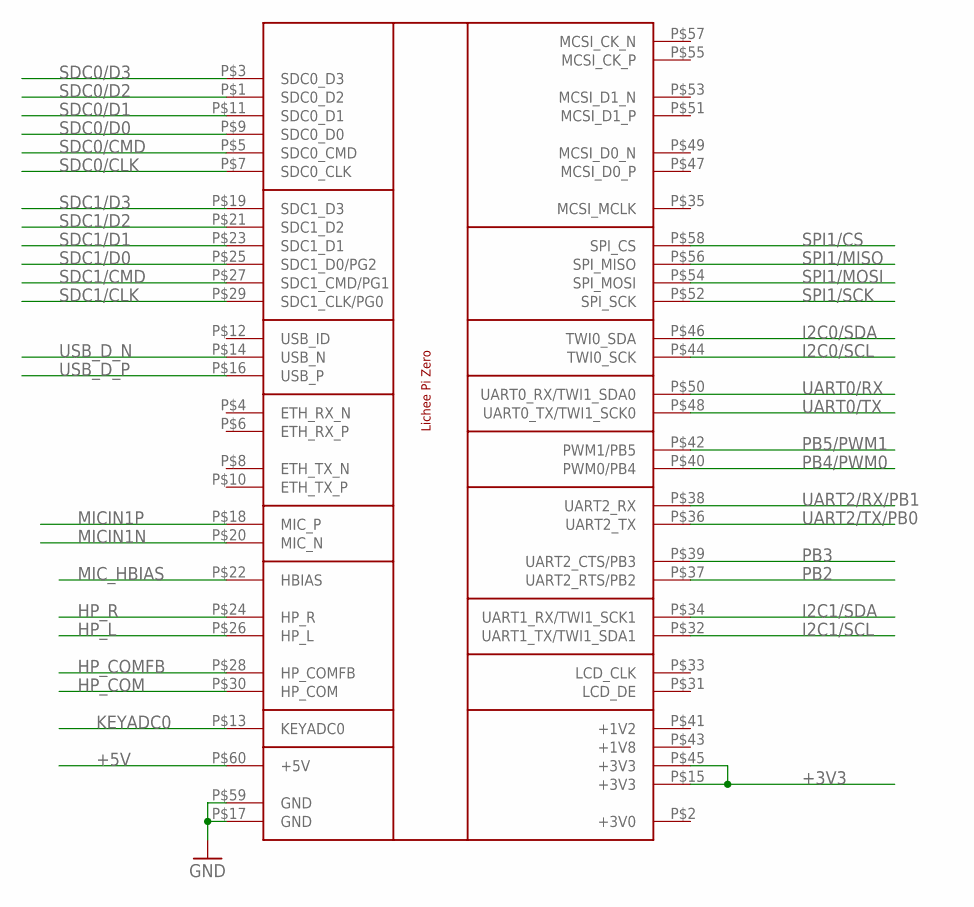
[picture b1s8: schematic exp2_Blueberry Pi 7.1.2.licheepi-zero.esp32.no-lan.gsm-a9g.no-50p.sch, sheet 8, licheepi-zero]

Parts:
U$22: LICHEE_ZERO

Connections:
+3V3: U$22.P$15 (+3V3), U$22.P$45 (+3V3); also elsewhere on the board
+5V: U$22.P$60 (+5V); also elsewhere on the board
GND: U$22.P$17 (GND), U$22.P$59 (GND); also elsewhere on the board
HP_COM: U$22.P$30 (HP_COM); also elsewhere on the board
HP_COMFB: U$22.P$28 (HP_COMFB); also elsewhere on the board
HP_L: U$22.P$26 (HP_L); also elsewhere on the board
HP_R: U$22.P$24 (HP_R); also elsewhere on the board
I2C0/SCL: U$22.P$44 (TWI0_SCK); also elsewhere on the board
I2C0/SDA: U$22.P$46 (TWI0_SDA); also elsewhere on the board
I2C1/SCL: U$22.P$32 (UART1_TX/TWI1_SDA1); also elsewhere on the board
I2C1/SDA: U$22.P$34 (UART1_RX/TWI1_SCK1); also elsewhere on the board
KEYADC0: U$22.P$13 (KEYADC0)
MICIN1N: U$22.P$20 (MIC_N); also elsewhere on the board
MICIN1P: U$22.P$18 (MIC_P); also elsewhere on the board
MIC_HBIAS: U$22.P$22 (HBIAS); also elsewhere on the board
PB2: U$22.P$37 (UART2_RTS/PB2); also elsewhere on the board
PB3: U$22.P$39 (UART2_CTS/PB3); also elsewhere on the board
PB4/PWM0: U$22.P$40 (PWM0/PB4); also elsewhere on the board
PB5/PWM1: U$22.P$42 (PWM1/PB5); also elsewhere on the board
SDC0/CLK: U$22.P$7 (SDC0_CLK); also elsewhere on the board
SDC0/CMD: U$22.P$5 (SDC0_CMD); also elsewhere on the board
SDC0/D0: U$22.P$9 (SDC0_D0); also elsewhere on the board
SDC0/D1: U$22.P$11 (SDC0_D1); also elsewhere on the board
SDC0/D2: U$22.P$1 (SDC0_D2); also elsewhere on the board
SDC0/D3: U$22.P$3 (SDC0_D3); also elsewhere on the board
SDC1/CLK: U$22.P$29 (SDC1_CLK/PG0); also elsewhere on the board
SDC1/CMD: U$22.P$27 (SDC1_CMD/PG1); also elsewhere on the board
SDC1/D0: U$22.P$25 (SDC1_D0/PG2); also elsewhere on the board
SDC1/D1: U$22.P$23 (SDC1_D1); also elsewhere on the board
SDC1/D2: U$22.P$21 (SDC1_D2); also elsewhere on the board
SDC1/D3: U$22.P$19 (SDC1_D3); also elsewhere on the board
SPI1/CS: U$22.P$58 (SPI_CS); also elsewhere on the board
SPI1/MISO: U$22.P$56 (SPI_MISO); also elsewhere on the board
SPI1/MOSI: U$22.P$54 (SPI_MOSI); also elsewhere on the board
SPI1/SCK: U$22.P$52 (SPI_SCK); also elsewhere on the board
UART0/RX: U$22.P$50 (UART0_RX/TWI1_SDA0); also elsewhere on the board
UART0/TX: U$22.P$48 (UART0_TX/TWI1_SCK0); also elsewhere on the board
UART2/RX/PB1: U$22.P$38 (UART2_RX); also elsewhere on the board
UART2/TX/PB0: U$22.P$36 (UART2_TX); also elsewhere on the board
USB_D_N: U$22.P$14 (USB_N); also elsewhere on the board
USB_D_P: U$22.P$16 (USB_P); also elsewhere on the board

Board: 2 copper layers, 91 parts (41 on the bottom side), 122 nets, no tracks yet.

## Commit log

2020-09-14 use CPU module Lichee-Pi-Zero to faster and easier build
    exp2_Blueberry Pi 7.1.2.licheepi-zero.esp32.no-lan.gsm-a9g.no-50p

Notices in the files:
parts and their libraries:
SparkFun-Connectors: Licensing: Creative Commons ShareAlike 4.0 International - https://creativecommons.org/licenses/by-sa/4.0
esp32-1: Creative Commons Attribution-ShareAlike 4.0 International
memory-winbond: Copyright (C) 2010, Bob Starr
supply0: Copyright (C) 2007, Bob Starr
